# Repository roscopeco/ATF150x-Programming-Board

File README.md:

## JTAG Programming & Testing Board for ATF1502 & 1504 CPLDs

### What

This is a small board to support JTAG programming (tested with Microchip ATDH1150USB) 
and general testing of ATF15xx CPLDs.

PLCC44 and PLCC84 variants are directly supported. Power can come from DuPonts, a
5V barrel jack or USB-C.

Board is four layer, and should be easily manufacturable by pretty much any fab you
care to use (I like JLCPCB, YMMV). It's quite small so should be reasonably cheap,
and all components are through-hole so nice and easy to solder.

The are really the last good 5V CPLDs that are in production - make use of them,
encourage Microchip to not discontinue them!

* [ATF1502](https://www.microchip.com/en-us/product/atf1502as)
* [ATF1504](https://www.microchip.com/en-us/product/atf1504as)

### Why?

I needed a board to do some testing with ATF1504 CPLDs for a new 
[rosco_m68k](https://github.com/rosco-m68k/rosco_m68k) thing I was
working on, and thought it might also be useful to others. So here you go.

### Who

Copyright (c)2024 Ross Bamford
Licensed under the Strongly Reciprocal CERN-OHL-S license. 
See LICENSE.md for details

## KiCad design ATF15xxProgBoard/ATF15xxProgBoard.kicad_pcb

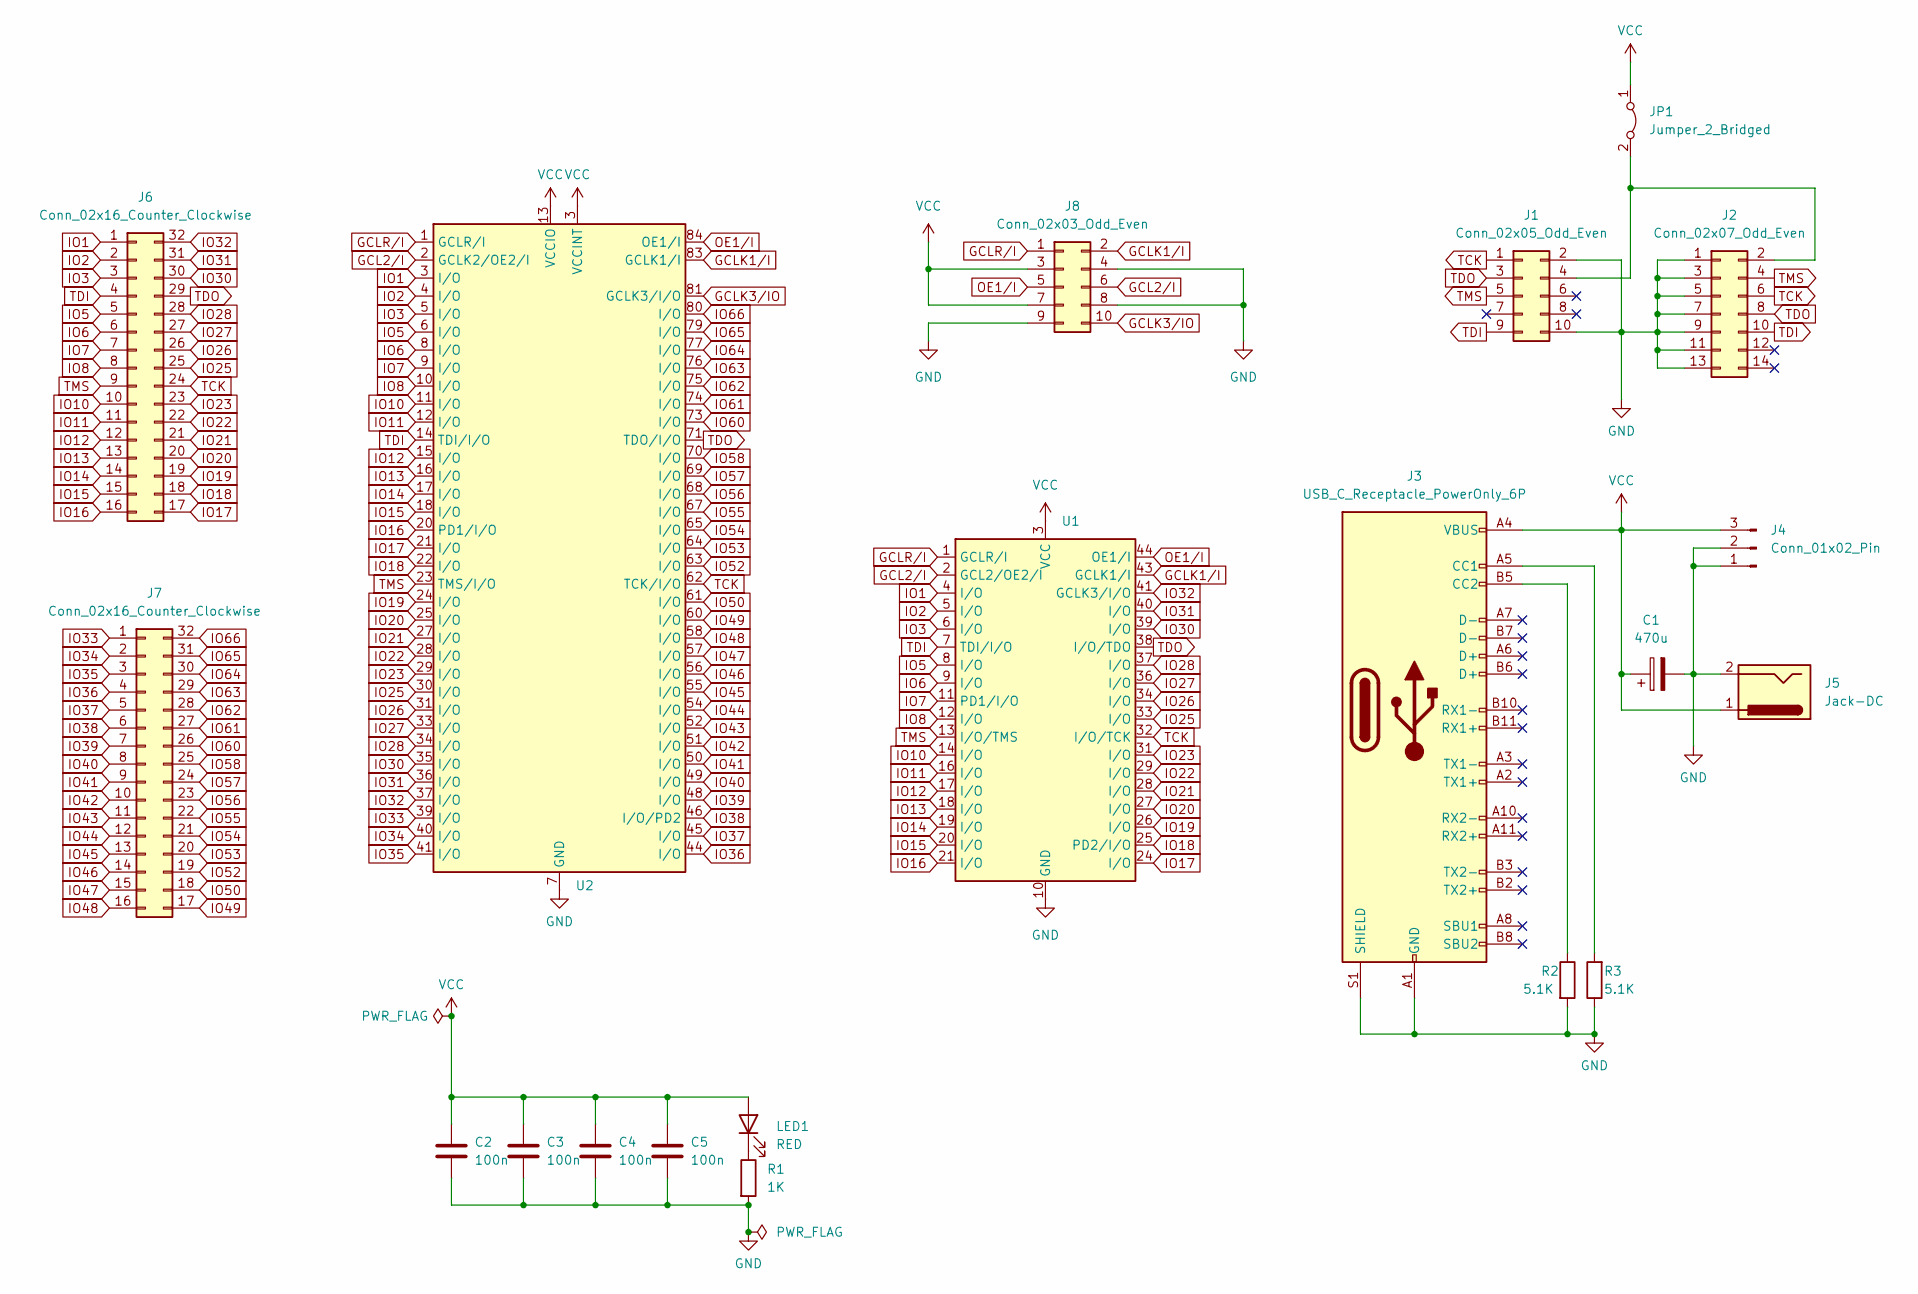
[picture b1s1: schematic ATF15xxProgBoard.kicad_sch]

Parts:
C1: 470u; CP_Radial_D10.0mm_P3.80mm
C2, C3, C4, C5: 100n; C_Rect_L4.0mm_W2.5mm_P2.50mm
J1: Conn_02x05_Odd_Even; IDC-Header_2x05_P2.54mm_Vertical
J2: Conn_02x07_Odd_Even; IDC-Header_2x07_P2.54mm_Vertical
J3: USB_C_Receptacle_PowerOnly_6P; USB_C_Receptacle_Palconn_UTC16-G
J4: Conn_01x02_Pin; PinHeader_1x03_P2.54mm_Vertical
J5: Jack-DC; BarrelJack_Horizontal
J6, J7: Conn_02x16_Counter_Clockwise; PinHeader_2x16_P2.54mm_Vertical
J8: Conn_02x03_Odd_Even; PinHeader_2x05_P2.54mm_Vertical
JP1: Jumper_2_Bridged; PinHeader_1x02_P2.54mm_Vertical
LED1: RED; LED_D5.0mm
R1: 1K; R_Axial_DIN0207_L6.3mm_D2.5mm_P10.16mm_Horizontal
R2, R3: 5.1K; R_Axial_DIN0207_L6.3mm_D2.5mm_P10.16mm_Horizontal
U1: PLCC-44_THT-Socket
U2: PLCC-84_THT-Socket

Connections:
GCL2/I: J8.6, U1.2 (GCL2/OE2/I), U2.2 (GCLK2/OE2/I)
GCLK1/I: J8.2, U1.43 (GCLK1/I), U2.83 (GCLK1/I)
GCLK3/IO: J8.10, U2.81 (GCLK3/I/O)
GCLR/I: J8.1, U1.1 (GCLR/I), U2.1 (GCLR/I)
GND: C1.2, C2.2, C3.1, C4.2, C5.2, J1.2, J1.10, J2.1, J2.3, J2.5, J2.7, J2.9, J2.11, J2.13, J3.A1 (GND), J3.A12 (GND), J3.B1 (GND), J3.B12 (GND), J3.S1 (SHIELD), J4.1, J4.2, J5.2, J8.4, J8.8, J8.9, R1.2, R2.2, R3.1, U1.10 (GND), U1.22 (GND), U1.30 (GND), U1.42 (GND), U2.7 (GND), U2.19 (GND), U2.32 (GND), U2.42 (GND), U2.47 (GND), U2.59 (GND), U2.72 (GND), U2.82 (GND)
IO2: J6.2, U1.5 (I/O), U2.4 (I/O)
IO3: J6.3, U1.6 (I/O), U2.5 (I/O)
IO5: J6.5, U1.8 (I/O), U2.6 (I/O)
IO6: J6.6, U1.9 (I/O), U2.8 (I/O)
IO7: J6.7, U1.11 (PD1/I/O), U2.9 (I/O)
IO8: J6.8, U1.12 (I/O), U2.10 (I/O)
IO10: J6.10, U1.14 (I/O), U2.11 (I/O)
IO11: J6.11, U1.16 (I/O), U2.12 (I/O)
IO12: J6.12, U1.17 (I/O), U2.15 (I/O)
IO13: J6.13, U1.18 (I/O), U2.16 (I/O)
IO14: J6.14, U1.19 (I/O), U2.17 (I/O)
IO15: J6.15, U1.20 (I/O), U2.18 (I/O)
IO16: J6.16, U1.21 (I/O), U2.20 (PD1/I/O)
IO17: J6.17, U1.24 (I/O), U2.21 (I/O)
IO18: J6.18, U1.25 (PD2/I/O), U2.22 (I/O)
IO19: J6.19, U1.26 (I/O), U2.24 (I/O)
IO20: J6.20, U1.27 (I/O), U2.25 (I/O)
IO21: J6.21, U1.28 (I/O), U2.27 (I/O)
IO22: J6.22, U1.29 (I/O), U2.28 (I/O)
IO23: J6.23, U1.31 (I/O), U2.29 (I/O)
IO25: J6.25, U1.33 (I/O), U2.30 (I/O)
IO26: J6.26, U1.34 (I/O), U2.31 (I/O)
IO27: J6.27, U1.36 (I/O), U2.33 (I/O)
IO28: J6.28, U1.37 (I/O), U2.34 (I/O)
IO30: J6.30, U1.39 (I/O), U2.35 (I/O)
IO31: J6.31, U1.40 (I/O), U2.36 (I/O)
IO32: J6.32, U1.41 (GCLK3/I/O), U2.37 (I/O)
IO33: J7.1, U2.39 (I/O)
IO34: J7.2, U2.40 (I/O)
IO35: J7.3, U2.41 (I/O)
IO36: J7.4, U2.44 (I/O)
IO37: J7.5, U2.45 (I/O)
IO38: J7.6, U2.46 (I/O/PD2)
IO39: J7.7, U2.48 (I/O)
IO40: J7.8, U2.49 (I/O)
IO41: J7.9, U2.50 (I/O)
IO42: J7.10, U2.51 (I/O)
IO43: J7.11, U2.52 (I/O)
IO44: J7.12, U2.54 (I/O)
IO45: J7.13, U2.55 (I/O)
IO46: J7.14, U2.56 (I/O)
IO47: J7.15, U2.57 (I/O)
IO48: J7.16, U2.58 (I/O)
IO49: J7.17, U2.60 (I/O)
IO50: J7.18, U2.61 (I/O)
IO52: J7.19, U2.63 (I/O)
IO53: J7.20, U2.64 (I/O)
IO54: J7.21, U2.65 (I/O)
IO55: J7.22, U2.67 (I/O)
IO56: J7.23, U2.68 (I/O)
IO57: J7.24, U2.69 (I/O)
IO58: J7.25, U2.70 (I/O)
IO60: J7.26, U2.73 (I/O)
IO61: J7.27, U2.74 (I/O)
IO62: J7.28, U2.75 (I/O)
IO63: J7.29, U2.76 (I/O)
IO64: J7.30, U2.77 (I/O)
IO65: J7.31, U2.79 (I/O)
IO66: J7.32, U2.80 (I/O)
unnamed: J1.4, J2.2, JP1.2 (B)
unnamed: J3.A5 (CC1), R3.2
unnamed: J3.B5 (CC2), R2.1
unnamed: LED1.1 (K), R1.1
OE1/I: J8.5, U1.44 (OE1/I), U2.84 (OE1/I)
TCK: J1.1, J2.6, J6.24, U1.32 (I/O/TCK), U2.62 (TCK/I/O)
TDI: J1.9, J2.10, J6.4, U1.7 (TDI/I/O), U2.14 (TDI/I/O)
TDO: J1.3, J2.8, J6.29, U1.38 (I/O/TDO), U2.71 (TDO/I/O)
TMS: J1.5, J2.4, J6.9, U1.13 (I/O/TMS), U2.23 (TMS/I/O)

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
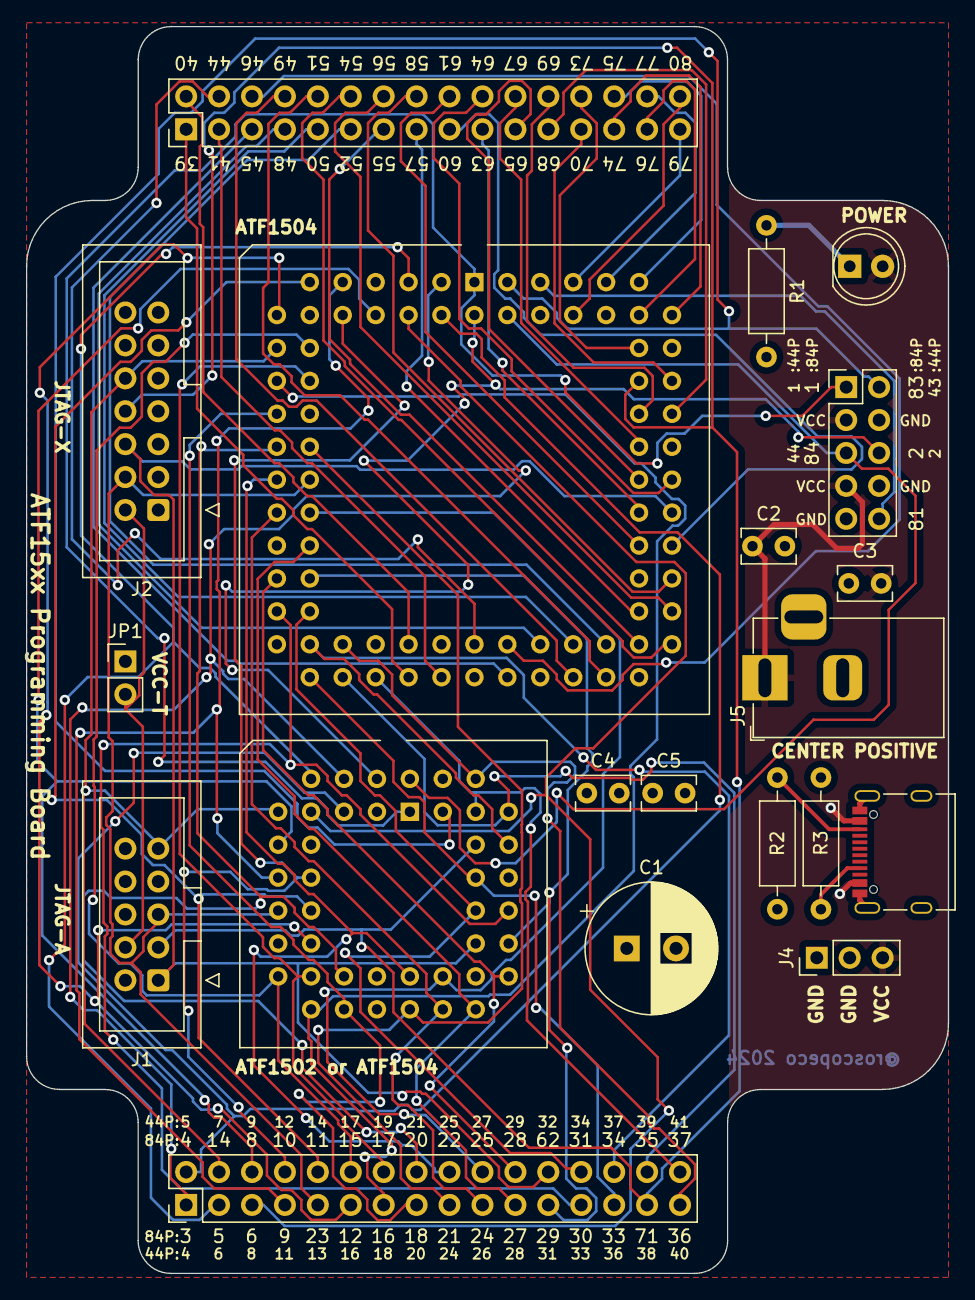
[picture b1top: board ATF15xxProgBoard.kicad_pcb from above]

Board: 4 copper layers, 71.1 x 96.2 mm, 20 parts (0 on the bottom side), 75 nets.

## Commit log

2024-03-10 Initial ignorance
2024-03-10 Initial import
2024-03-10 Ignore locks
2024-03-10 Add readme, license
2024-03-10 Add PDF
